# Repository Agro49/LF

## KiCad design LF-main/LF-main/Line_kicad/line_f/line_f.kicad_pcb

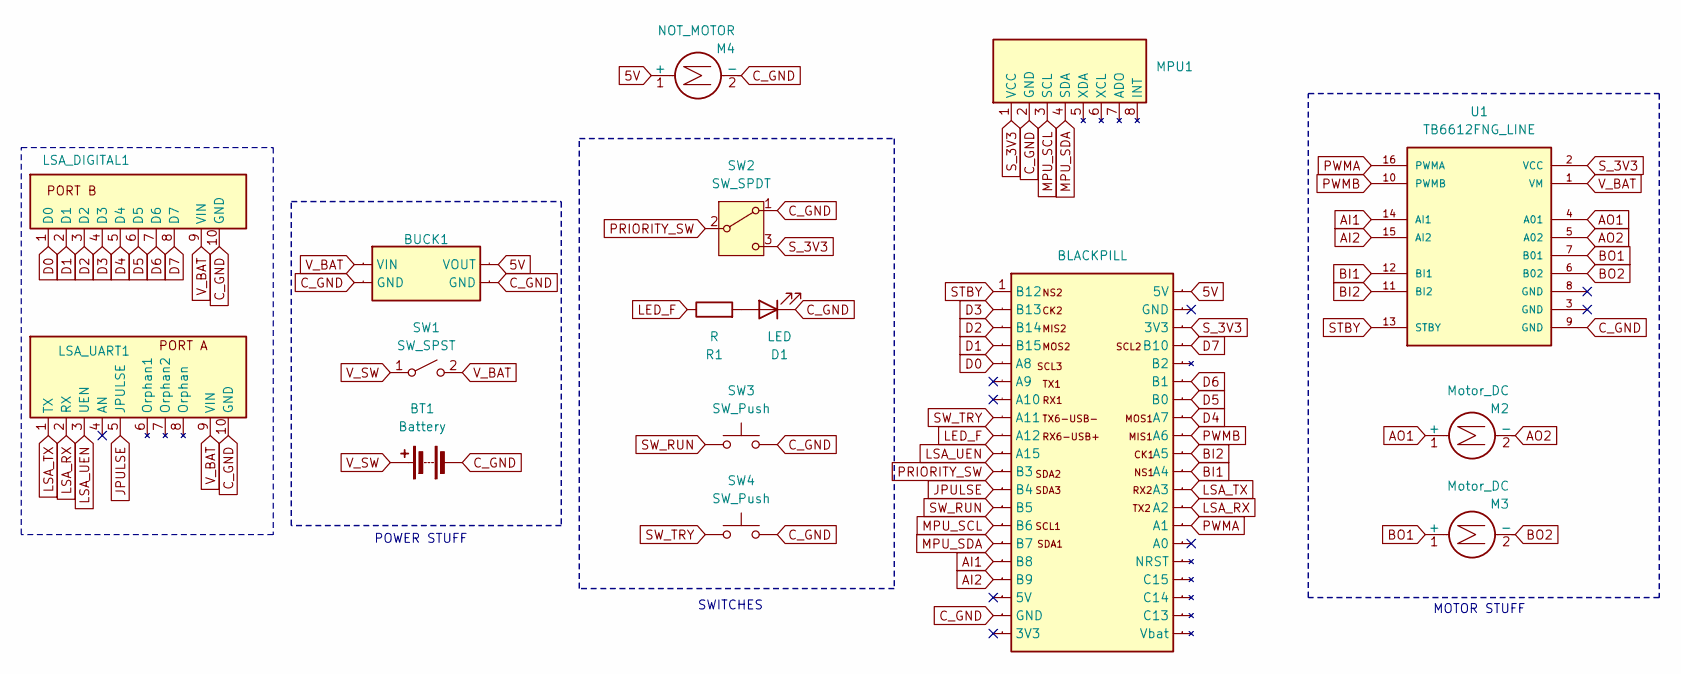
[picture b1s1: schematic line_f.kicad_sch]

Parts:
BT1: Battery; BATTERY_LINE_XT60
BUCK1: BUCK_SMD
D1: LED; LED_LINE
LSA_DIGITAL1: LSA_DIGITAL
LSA_UART1: LSA_UART
M2, M3: Motor_DC; connector_motor
M4: NOT_MOTOR; connector_motor
MPU1: MPU6050_AR
R1: R; RESISTOR_LINE
SW1: SW_SPST; battery_sw
SW2: SW_SPDT; SLIDE SW
SW3, SW4: SW_Push; push_button
U1: TB6612FNG_LINE; PARTREV 11-13-17
m1: BLACKPILL; FINAL_BLACKPILL_LINE; Manufacturer Part Black Pill V3

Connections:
5V: BUCK1.2 (VOUT), M4.1 (+), m1.21 (5V)
AI1: U1.14 (AI1), m1.16 (B8)
AI2: U1.15 (AI2), m1.17 (B9)
AO1: M2.1 (+), U1.4 (A01)
AO2: M2.2 (-), U1.5 (A02)
BI1: U1.12 (BI1), m1.31 (A4)
BI2: U1.11 (BI2), m1.30 (A5)
BO1: M3.1 (+), U1.7 (B01)
BO2: M3.2 (-), U1.6 (B02)
C_GND: BT1.2 (-), BUCK1.3 (GND), BUCK1.4 (GND), D1.1 (K), LSA_DIGITAL1.10 (GND), LSA_UART1.10 (GND), M4.2 (-), MPU1.2 (GND), SW2.1 (A), SW3.2, SW4.2, U1.9 (GND), m1.19 (GND)
D0: LSA_DIGITAL1.1 (D0), m1.5 (A8)
D1: LSA_DIGITAL1.2 (D1), m1.4 (B15)
D2: LSA_DIGITAL1.3 (D2), m1.3 (B14)
D3: LSA_DIGITAL1.4 (D3), m1.2 (B13)
D4: LSA_DIGITAL1.5 (D4), m1.28 (A7)
D5: LSA_DIGITAL1.6 (D5), m1.27 (B0)
D6: LSA_DIGITAL1.7 (D6), m1.26 (B1)
D7: LSA_DIGITAL1.8 (D7), m1.24 (B10)
JPULSE: LSA_UART1.5 (JPULSE), m1.12 (B4)
LED_F: R1.1, m1.9 (A12)
LSA_RX: LSA_UART1.2 (RX), m1.33 (A2)
LSA_TX: LSA_UART1.1 (TX), m1.32 (A3)
LSA_UEN: LSA_UART1.3 (UEN), m1.10 (A15)
MPU_SCL: MPU1.3 (SCL), m1.14 (B6)
MPU_SDA: MPU1.4 (SDA), m1.15 (B7)
unnamed: D1.2 (A), R1.2
PRIORITY_SW: SW2.2 (B), m1.11 (B3)
PWMA: U1.16 (PWMA), m1.34 (A1)
PWMB: U1.10 (PWMB), m1.29 (A6)
STBY: U1.13 (STBY), m1.1 (B12)
SW_RUN: SW3.1, m1.13 (B5)
SW_TRY: SW4.1, m1.8 (A11)
S_3V3: MPU1.1 (VCC), SW2.3 (C), U1.2 (VCC), m1.23 (3V3)
V_BAT: BUCK1.1 (VIN), LSA_DIGITAL1.9 (VIN), LSA_UART1.9 (VIN), SW1.2 (B), U1.1 (VM)
V_SW: BT1.1 (+), SW1.1 (A)

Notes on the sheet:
MOTOR STUFF
SWITCHES
POWER STUFF

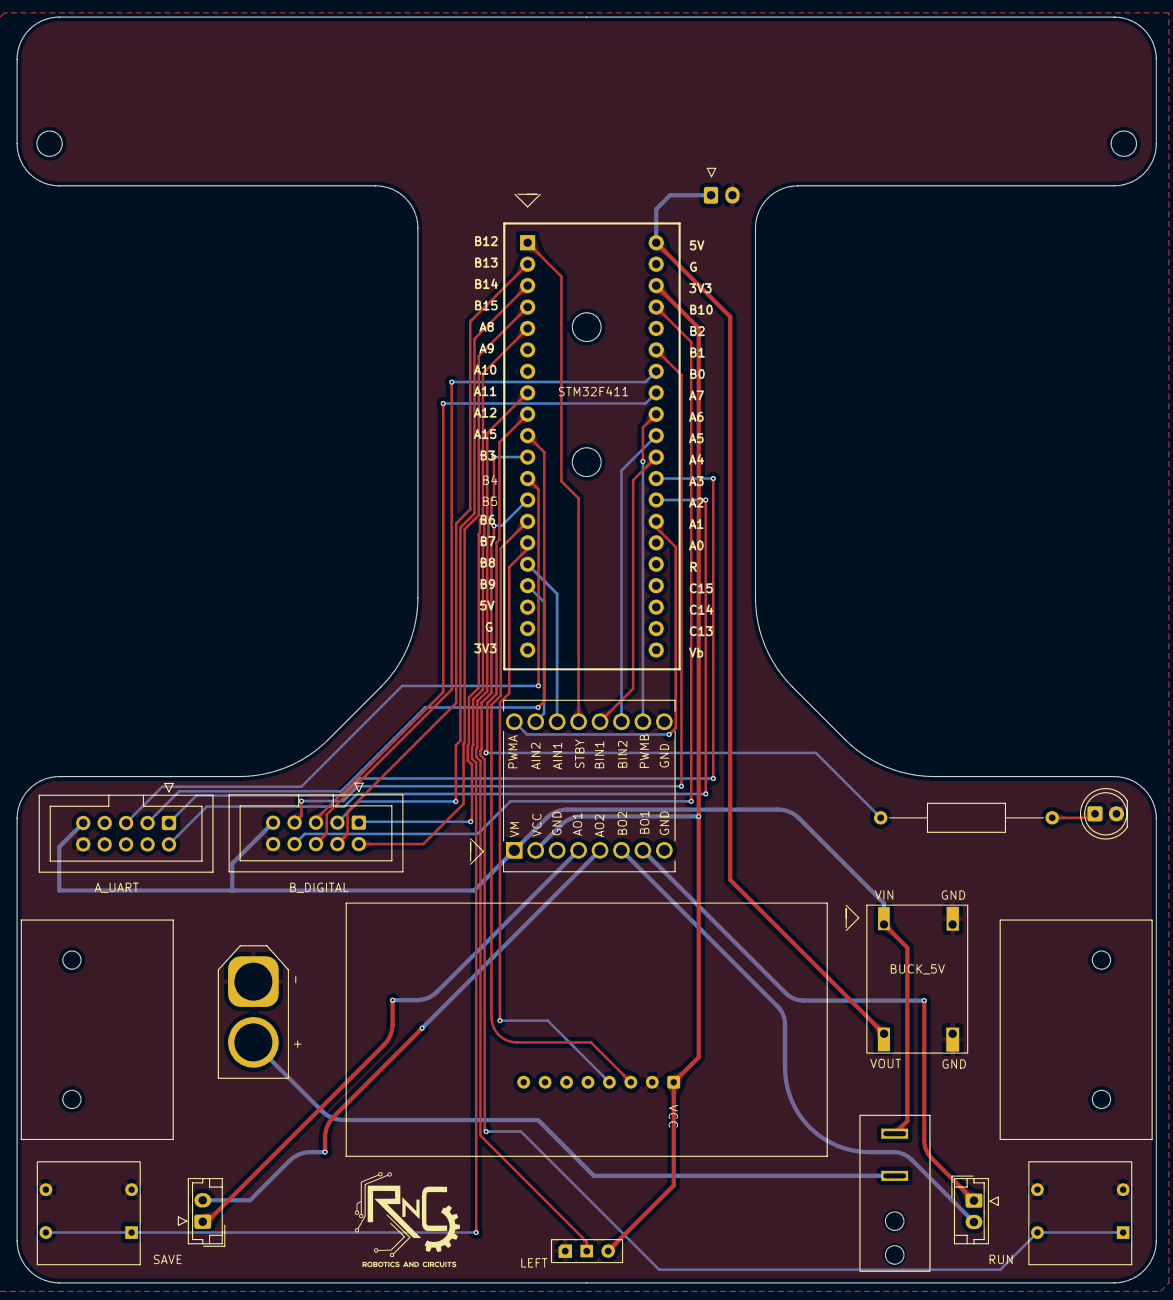
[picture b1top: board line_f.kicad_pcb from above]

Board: 2 copper layers, 135.0 x 150.0 mm, 16 parts (1 on the bottom side), 35 nets.

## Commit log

2025-02-21 v9.0
2025-02-21 pin1
2025-02-21 6updatefrmsch#
2025-02-21 6halfshape#
2025-02-21 6baseshape#
2025-02-21 6baseshapefinal#
2025-02-21 6alignedcaster#
2025-02-22 rev2
2025-02-22 6wheelfinal#
2025-02-22 6semifshapepos#
2025-02-22 6semifshapepos-2#
2025-02-22 6lsaholes-final#
2025-02-22 7battery-center#
2025-02-22 7r-start#
2025-02-22 7r-start.5#
2025-02-23 7r-start.77#
2025-02-23 7r-start.87#
2025-02-23 7r-mpufix.87#
2025-02-23 7r-mpufix.89#
2025-02-23 7r-logo.89#
2025-02-23 789#
2025-02-23 8TEARDROPS#
2025-02-23 8updatelogo#
2025-02-23 8final#
